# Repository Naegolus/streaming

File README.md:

# Streaming

Brainstorming repository

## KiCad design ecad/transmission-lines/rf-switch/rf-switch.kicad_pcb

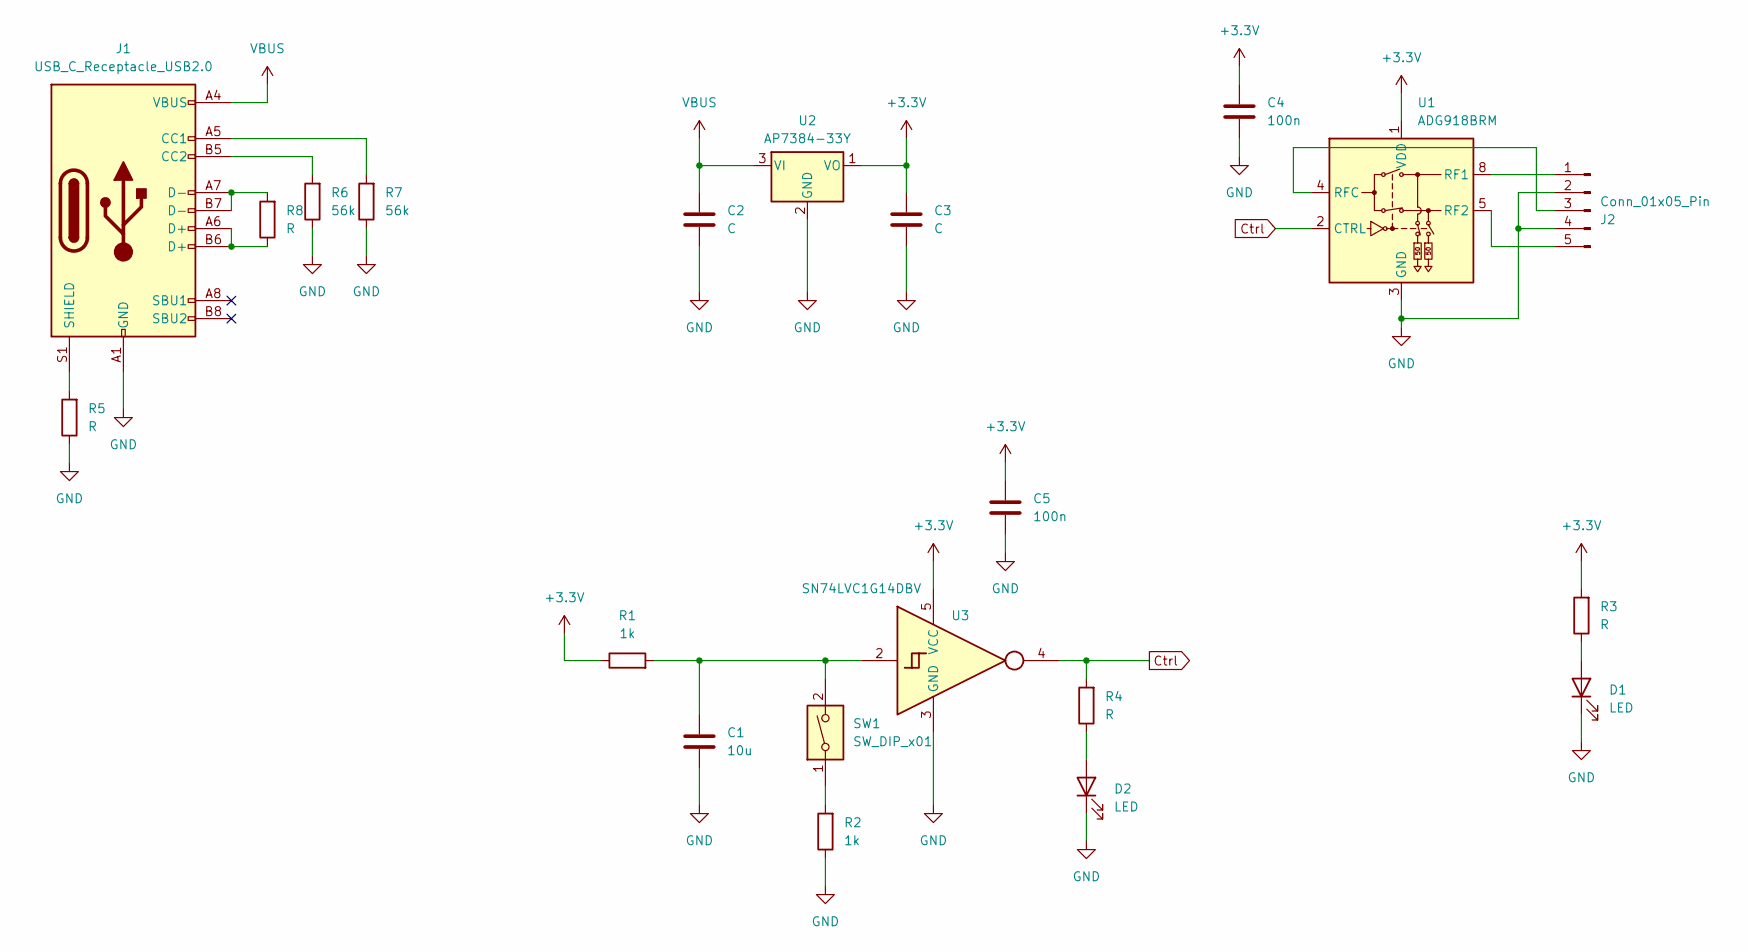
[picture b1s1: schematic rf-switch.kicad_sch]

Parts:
C1: 10u; C_0603_1608Metric_Pad1.08x0.95mm_HandSolder
C2, C3: C; C_0603_1608Metric_Pad1.08x0.95mm_HandSolder
C4, C5: 100n; C_0603_1608Metric_Pad1.08x0.95mm_HandSolder
D1, D2: LED; LED_D3.0mm_FlatTop
J1: USB_C_Receptacle_USB2.0; USB_C_Receptacle_GCT_USB4105-xx-A_16P_TopMnt_Horizontal
J2: Conn_01x05_Pin; PinHeader_1x05_P2.54mm_Horizontal
R1, R2: 1k; R_0603_1608Metric_Pad0.98x0.95mm_HandSolder
R3, R4, R5, R8: R; R_0603_1608Metric_Pad0.98x0.95mm_HandSolder
R6, R7: 56k; R_0603_1608Metric_Pad0.98x0.95mm_HandSolder
SW1: SW_DIP_x01; SW_PUSH_6mm_H4.3mm
U1: ADG918BRM; MSOP-8_3x3mm_P0.65mm
U2: AP7384-33Y; SOT-89-3
U3: SN74LVC1G14DBV; SOT-23-5

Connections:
+3.3V: C3.1, C4.1, C5.1, R1.1, R3.2, U1.1 (VDD), U2.1 (VO), U3.5 (VCC)
Ctrl: R4.2, U1.2 (CTRL), U3.4
GND: C1.2, C2.2, C3.2, C4.2, C5.2, D1.1 (K), D2.1 (K), J1.A1 (GND), J1.A12 (GND), J1.B1 (GND), J1.B12 (GND), J2.2, J2.4, R2.1, R5.1, R6.1, R7.1, U1.3 (GND), U1.6 (GND), U1.7 (GND), U2.2 (GND), U3.3 (GND)
unnamed: C1.1, R1.2, SW1.2, U3.2
unnamed: D1.2 (A), R3.1
unnamed: D2.2 (A), R4.1
unnamed: J1.A5 (CC1), R7.2
unnamed: J1.B5 (CC2), R6.2
unnamed: J1.A6 (D+), J1.B6 (D+), R8.1
unnamed: J1.A7 (D-), J1.B7 (D-), R8.2
unnamed: J1.S1 (SHIELD), R5.2
unnamed: J2.1, U1.8 (RF1)
unnamed: J2.3, U1.4 (RFC)
unnamed: J2.5, U1.5 (RF2)
unnamed: R2.2, SW1.1
VBUS: C2.1, J1.A4 (VBUS), J1.A9 (VBUS), J1.B4 (VBUS), J1.B9 (VBUS), U2.3 (VI)

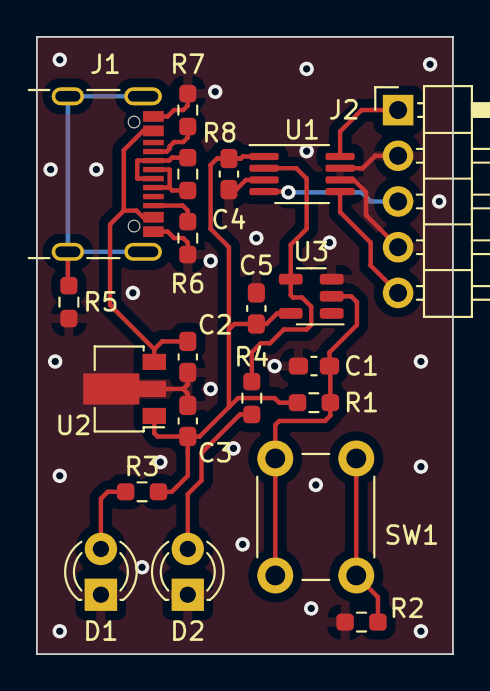
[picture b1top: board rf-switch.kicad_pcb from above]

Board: 2 copper layers, 23.1 x 34.3 mm, 21 parts (0 on the bottom side), 16 nets.

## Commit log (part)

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2022-04-08 Set temp USB topology
2022-04-08 Update video files
2022-04-15 Implement cable holder
2022-04-15 Add half bridge soldering concept
2022-04-15 Add cable holder assembly file
2022-04-15 Add CubeMX auto-install
2022-04-19 Add cable-holder-2
2022-04-19 New version of hw-cam-mounting
2022-04-19 Add test-adapter-box
2022-04-19 Add result
2022-04-26 Update video devices
2022-04-26 CAD: Improve test adapter box
2022-04-28 Add rigol repair pics
2022-04-28 Update video dev settings
2022-04-28 hw: Add pics
2022-04-29 ecad: Add hot plate stuff
2022-04-29 cad: Add rotary encoder knob
2022-04-29 cad: move knob
2022-05-03 Update video device settings
2022-05-10 Add pictures
2022-05-12 Add cpx400dp infos
2022-06-08 cad: Add z-leveling
2022-06-08 ecad: Add datasheet
2022-06-08 cad: Cable holder 2. Add hook
2022-06-09 Add oscilloscope screenshot
2022-06-09 Fix document
2022-06-10 Beautify document
2022-06-10 Add transmission scene
2022-06-10 Fix doc
2022-06-14 ecad: Add bitcoin miner pic
2022-06-14 ecad: Add transmission line scene
2022-06-27 Add BSc Presentation
2022-06-27 Add BSc
2022-06-27 Update gitignore
2022-06-27 Add SCARTS (SPEAR2) doc
2022-06-27 Add app1 vhdl part
2022-06-27 Add src files
2022-07-05 cad: Rename debugging box directory
2022-07-05 docker: Switch from bullseye to testing
2022-07-05 docker: Switch from podman
2022-07-05 scarts32/doc: Add SDRAM datasheet
2022-07-05 dm4Flashing: Add pics
2022-07-05 cad: Fix cable position
2022-07-06 cad: lib: fix rcube(). Thx bananenbär!
2022-07-06 cad: lib-test: add rcube() test
2022-07-07 Add led tutorial code
2022-07-07 Add Discman 4 flashing tool
2022-07-08 dm4Flashing: Relicense one file MIT -> GPLv3
2022-07-08 Remove unused line in dm4Flashing()
2022-07-12 led-test: Simplify
2022-07-12 dm4Flashing(): Activate LEDs
2022-07-12 dm4Flashing(): Import LED lib
2022-07-12 dm4Flashing(): Use production file
2022-07-12 Processing(): Flush log outputs
2022-07-12 dm4Flashing(): Add service file. Thx Banana!
2022-07-12 dm4Flashing(): Add plantuml diagrams
2022-07-12 dm4Flashing(): Improve
2022-07-13 cad: Add flashing box pic
2022-07-14 dm4Flashing(): Add old ST Link v2 firmware
2022-07-14 dm4Flashing(): Replace ST Link firmware
2022-07-21 sw: Add Processing()
2022-07-21 sw: Add Greeting()
2022-08-16 Add core files
2022-08-16 tools: Add process template script
2022-08-16 Greeting: Fix path in meson.build
2022-08-16 Gaming: First version
2022-08-17 Gaming: Print license text
2022-08-17 Gaming: Add and start GameServing()
2022-08-17 SystemDebugging(): Don't show in process tree
2022-08-17 SystemDebugging(): Fix proc tree display
2022-08-17 GameServing(): Remove function shutdown()
2022-08-17 TicTacToeGaming(): Change listening port
2022-08-17 GameSupervising(): Don't start TicTacToeGaming()
2022-08-17 TicTacToeGaming(): Cleanup
2022-08-17 TicTacToeGaming(): Inherit Gaming()
2022-08-18 GamerInteracting(): Improve debug output
2022-08-20 Pipe: Add atomic function get
2022-08-20 Gaming(): Catch exceptions
2022-08-20 GamerInteracting(): Add several functions
    1. Add terminal settings (Hide cursor)
    2. First welcome screen
    3. Name setting
2022-08-20 ServerSelecting(): Add
2022-08-20 GamerInteracting(): Beautify debug output
2022-08-20 ServerSelecting(): Rename to GameSelecting()
2022-08-20 GameServing(): Move gamer list to GamerInteracting() static area
2022-08-20 SystemDebugging(): Don't use function procTreeDisplaySet() internally
2022-08-20 Beautify dbg output
2022-08-20 Gaming(): Stuff
2022-08-20 GamerInteracting(): Improve name setting screen
2022-08-20 GameSelecting(): Remove function shutdown
2022-08-20 Gaming(): Add mutex
2022-08-22 GamerInteracting(): Set terminal title
2022-08-22 GamerInteracting(): Show GameSelecting()
2022-08-22 Processing(): Add state macros
2022-08-22 GamerInteracting(): Use state macros
2022-08-22 GameSelecting(): Add states
2022-08-22 Gaming(): Implement stuff
2022-08-22 Stuffedi stuff
2022-08-22 GameSelecting(): Types list screen
2022-08-22 TicTacToeGaming(): Move to dir games
2022-08-22 GameSelecting(): Add game id
2022-08-22 Gaming(): Add pFctCreate
2022-08-23 Do stuff
2022-08-23 GameSelecting(): Implement type list
2022-08-23 GameSelecting(): Create result
2022-08-23 GamerInteracting(): Implement server create message
2022-08-24 GameSelecting(): Keep negative ifs
2022-08-24 GameServing(): Flush data completely
2022-08-25 GamerInteracting(): Remove magic number
2022-08-25 GameServing(): Fix endless loop
2022-08-25 GameSelecting(): Implement game name setting
2022-08-25 GameServing(): Process msg create
2022-08-25 GameServing(): Close message loop
2022-08-25 ConnectFourGaming(): Implement base states
2022-08-25 ConnectFourGaming(): Implement welcome screen
2022-08-25 GameSelecting(): Fix games list screen
2022-08-25 GameServing(): Implement skeleton further
2022-08-25 Gaming(): Add gameConfig.json
2022-08-25 GameSelecting(): Implement Refresh
2022-08-25 GameSelecting(): Fix server list
2022-08-25 Gaming(): Implement game connecting
2022-08-27 doc: Add ssh paper
2022-09-12 Gaming(): Add ConnectFourLobbying()
2022-09-12 ConnectFourGaming(): Print game state in debug info
2022-09-12 ConnectFourLobbying(): Add state machine
2022-09-12 ConnectFourLobbying(): Init game structure
2022-09-12 ConnectFourLobbying(): Fix frames
2022-09-13 ConnectFourLobbying(): New json structure
2022-09-13 GameSelecting(): Fix SEGV on enter while no game present
2022-09-13 LibGaming: Add function keyIsNum()
2022-09-13 LibGaming: Add function keyIsCtrl()
2022-09-13 GameServing(): Dispatch "disconnect" messages to gamer
2022-09-13 GamerInteracting(): Forward control keys as well
2022-09-13 ConnectFourGaming(): Repel lobby process as soon as it's finished
2022-09-13 ConnectFourLobbying(): Remove gamer on escape key
2022-09-13 ConnectFourLobbying(): Add dirty bit to game state structure
2022-09-13 ConnectFourGaming(): Don't move forward in state
2022-09-13 ConnectFourLobbying(): Admin can end the lobbying process
2022-09-13 ConnectFourLobbying(): Dirty at beginning
2022-09-14 Gaming(): Remove function gameProcess()
2022-09-14 GamerInteracting(): Send disconnect message on keyEsc
2022-09-14 ConnectFourLobbying(): Interpret disconnect message instead of keyEsc
2022-09-14 ConnectFourLobbying(): Add dirty flag to gamer
2022-09-14 GameServing(): Beautify
2022-09-14 GameServing(): Add return
2022-09-14 ConnectFourGaming(): Add debug info
2022-09-14 GameSelecting(): Beautify
2022-09-14 GameSelecting(): Fix types list navigation
2022-09-14 GameSelecting(): Reinitialize offset variables
2022-09-14 GameServing(): Uncomment additional types
2022-09-14 GameSelecting(): Add gamers count
2022-09-14 LibGaming: Add keyAbort and keyEnd
2022-09-15 ListIdx: Encapsulate list cursor / window logic
2022-09-15 LibGaming: Add function millis()
2022-09-16 doc: Add connect four gaming frame example
2022-09-16 doc: Save
2022-09-16 doc: Update
2022-09-19 TcpTransfering(): Use Transfering()
2022-09-19 LibGaming: Use Transering()
2022-09-19 Authorizing(): Add
2022-09-19 TelnetAuthorizing(): Add
2022-09-19 doc: Add strange comm
2022-09-19 GamerInteracting(): Use TelnetAuth()
2022-09-19 GameServing(): Update
2022-09-19 doc: Improve server list
2022-09-19 ConnectFourMatching(): Prepare input and frame functions
2022-09-19 ConnectFourLobbying(): Fix typo
2022-09-19 ConnectFourMatching(): Fix skipped frames
2022-09-19 ConnectFourMatching(): Fix typo
2022-09-19 ConnectFourMatching(): Remove magic numbers
2022-09-19 ConnectFourMatching(): Implement first version of msgBoard()
2022-09-19 ConnectFourMatching(): Implement stuff
2022-09-19 ConnectFourMatching(): Print cursor on correct position
2022-09-19 doc: Change others frame
2022-09-19 Gaming(): Save
2022-09-19 meson: Decrease proc tree buffer size
2022-09-19 ConnectFourMatching(): Limit number of teams
2022-09-19 meson: Increase proc tree buffer size
2022-09-19 ConnectFourMatching(): Fix non updating cursor
2022-09-19 ConnectFourMatching(): Beautify
2022-09-19 ConnectFourMatching(): Implement team cursor calculation
2022-09-20 Update meson files
2022-09-20 meson: Prepare for dist compliancy
2022-09-20 doc: Move files around
2022-09-20 doc: Update connect four matching frame
2022-09-20 ConnectFourMatching(): Implement function matchFinished()
2022-09-20 doc: Add screenshots
2022-09-20 ConnectFourLobbying(): Do not use function isMember()
2022-09-20 ConnectFourMatching(): Clear match object on match init
2022-09-20 ConnectFourMatching(): Set dirty bit on round start
2022-09-20 ConnectFourMatching(): Implement stats screen
2022-09-20 GameSelecting(): Fix SEGV on connection reset
2022-09-20 GameServing(): Set gamers game pointer to null if game disconnects
2022-09-20 ConnectFourMatching(): Fix help movement
2022-09-20 doc: Add screen
2022-09-20 LibGaming(): Activate key debug information
2022-09-20 doc: Add screens
2022-09-20 TelnetAuthorizing(): Support different backspace code
2022-09-20 doc: Remove screen
2022-09-20 GameServing(): Check mpGame pointer
2022-09-20 doc: Rename log
2022-09-21 ListIdx: Add function sizeJumpSet()
2022-09-21 GameSelecting(): Use function keyProcess()
2022-09-22 ListIdx: Add function winEndPrint()
2022-09-22 GameSelecting(): Use function winEndPrint()
2022-09-22 GameSelecting(): Use function cursorPrint()
2022-09-22 ListIdx: Beautify
2022-09-22 Fix updates
2022-09-22 Fix stuff
2022-09-26 Add PROJECT_CLOSED
2022-12-23 Add Advent Of Code Day 1 - 3
2022-12-23 AoC 2015: Add day 4
2022-12-23 AoC 2022: Add day 11 almost
2022-12-23 Add common
2022-12-23 AoC 2015: Add day 14
2022-12-23 Rename stuff
2022-12-23 AoC 2022: Add day 12 beginning
2022-12-23 Remove license
2022-12-23 Add prolog hello world
2022-12-23 AoC 2022: Add day 8
2022-12-23 AoC 2015: Add day 7
2022-12-23 AoC 2022: Fix day 11 part 2
2022-12-23 AoC 2015: Add day 10
2022-12-23 Add: AoC 2015/3/1 and 2015/3/2
2022-12-23 AoC 2015: Add day 13
2022-12-23 AoC: Add day 4
2022-12-23 AoC 2022: Add day 7
2022-12-23 HttpRequesting(): Style
2022-12-23 AoC: Add day 5
2022-12-23 AoC 2015: Add day 9 start
2022-12-23 Processing(): Go into state PsDownShutting earlier
2022-12-23 Style
2022-12-23 AoC 2015: Add day 9
2022-12-23 AoC 2022: Add day 10
2022-12-23 Remove screenshot
2022-12-23 AoC 2022: Add day 6
2022-12-23 led-test: Update ids
2022-12-23 AoC 2022: Add day 9
2022-12-23 Processing(): Fix priority in function childrenSuccess()
2022-12-23 Processing(): Do not remove child if undriven
    Remove child if
    - Undriven
    as well as
    - Unused
2023-02-28 dm4Flashing: Invert detection logic
    Check for
    "G030/G031/G041"
    instead of
    "unknown device"
2023-02-28 dm4Flashing: Improve process
    - Do not rely on function communicate()
    without timeout
    - Detect system failure
2023-02-28 dm4Flashing(): Implement USB device reset
2023-02-28 doc: Add stuff
2023-03-01 dm4Flashing(): Add read protect
2023-03-01 common: Sync
2023-03-15 dm4Flashing(): Finalize
2023-03-17 core: Sync
2023-04-26 Sync
2023-06-20 tools: Add obs-cli
2023-06-22 obs-cli: Remove scene switch during item toggle
2023-06-22 obs-cli: Add comments
2023-06-22 transmission line: Add pulse + short circuit
2023-06-26 transmission line: Fixes
2023-08-10 Add book suggestions
2023-08-10 tools: Update obs-cli
2023-08-17 cad: Move directory
2023-08-18 Finalize hw-conn-3
2023-08-23 Add hw-conn-3 result
2023-08-23 Stromi: Add datasheets
2023-08-31 stromi: Add screenshot
2023-08-31 cad: Add cable holder coax
2023-08-31 stromi: Add pulseSiglent.sh
2023-08-31 stromi: Add R = Z0
2023-09-15 Add FreeCAD files
2023-09-16 Update box-stromi
2023-09-21 cad: box-stromi aligned
2023-09-21 cad: box-stromi: Lower part
2023-09-21 Add 23-09-21 measurements
2023-09-21 cad: box-stromi: Add Upper
2023-09-21 cad: box-stromi: Add screenshots
2023-09-22 cad: box-stromi: Finalize
2023-09-22 cat: box-stromi: Add fotos
2023-10-05 Add PhyAnimating()
2023-10-05 Add Rigol.py
2023-10-06 Fix licenses
2023-10-12 DiracAnimating(): Horizontal layout
2023-10-12 Rigol.py: Add fft
2023-10-12 Rigol.py: Merge subplot 3 and 4
2023-10-12 Rigol.py: Remove ax2 and use abs() after fft()
2023-11-17 Improve Rigol.py
2023-11-30 Add book suggestion
2023-11-30 Update stromi pdf
2023-11-30 Add rf-switch
2023-12-14 gitignore: Add pdf
2023-12-14 rf-switch: Add screenshots
